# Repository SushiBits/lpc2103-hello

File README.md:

# lpc2103-hello

Firmware for the LPC2103 evaluation board in [hardware/](hardware/) — a
blinkenlight, eventually. The board is not the interesting part. The interesting
part is that a 2004-era ARM7TDMI-S is being driven through a project structure
that a freshly started Cortex-M3 project would recognise, built from open
components with exactly one exception.

## A Cortex-M project with an ARM7 inside

The LPC2103 predates CMSIS by roughly half a decade. Its core is ARM7TDMI-S,
which is ARMv4T: no NVIC, no SysTick, no CMSIS vector table, no core header,
and nothing in CMSIS-Core to include. NXP never published a CMSIS-Pack for the
LPC2000 line, and there is no vendor SVD to download — the ones that ever
existed shipped inside Keil MDK installs under a vendor licence.

None of that is hidden here, and the core layer is genuinely hand-written. But
above the core everything is laid out the way modern tooling expects:

| Modern Cortex-M habit | How this project does it |
| --- | --- |
| Device header generated from a CMSIS-SVD | [LPC2103.svd](contrib/platform/share/LPC2103.svd) → SVDConv → `LPC2103.h` |
| Interrupt handler table generated from the IRQn enum | [irqn](contrib/irqn) → `LPC2103_handlers.h` |
| `core_*.h` / `system_*.h` / device header layering | [core_arm7tdmi-s.h](contrib/platform/include/core_arm7tdmi-s.h), [system_LPC2103.h](contrib/platform/include/system_LPC2103.h) |
| Register structs, `*_Pos` / `*_Msk` macros, field enums | generated, straight from the SVD |
| Peripheral view in the debugger during bring-up | cortex-debug loading the same SVD over J-Link |
| Boot image that the chip actually starts | [lpcsum.py](contrib/platform/share/lpcsum.py) writes the vector checksum the boot loader demands |

So the device description, the register map, the interrupt table and the
debugger's peripheral view all come from one machine-readable file, the same way
they would on a Cortex-M part. The only place the 2005 is visible is the core
header: a few hundred lines of qualifiers and intrinsics restricted to what
ARMv4T can actually execute.

## The device description

[LPC2103.svd](contrib/platform/share/LPC2103.svd) is typed in by hand, section
by section, reading UM10161 — no vendor file, no conversion, no scraping. It
took around twenty late-night commits to cover the part, one peripheral per
commit: SYS, VIC, PCB, GPIO0, FIO0, UART0/1, I2C0/1, SPI, SSP, ADC, TIMER0-3,
WDT and RTC. All eighteen are described; every VIC channel the silicon
implements now has a name in the generated `IRQn_Type`.

Because the document is hand-built, the manual was treated as a source to be
checked rather than trusted. Several of its own tables disagree with each other,
and a blank LPC2103 on a J-Link settles those arguments in about a minute:

| Question | Manual | Silicon |
| --- | --- | --- |
| PCONP reset value | `0x03BE` in the register summary, `0x001817BE` in the bit table | **`0x00C8179E`** |
| `SSPRIS` reset value | `0x04` in the register map, `TXRIS` = 1 in the bit table | **`0x08`** |
| Timer 2/3 counter width | 16-bit chapter, but a 32-bit counter paragraph copied in | **16 bits** |

The SVD records the measured values, and the commit messages say where the
number came from. The one thing silicon cannot settle is register *naming* —
which is why the VIC's two `VectAddr` registers had to be disambiguated by hand.

## How the pieces are produced

```
 LPC2103.svd ──SVDConv──▶ LPC2103.h ──irqn──▶ LPC2103_handlers.h
      │                      │                      │
      │                      └── includes ──▶ core_other.h ──▶ core_arm7tdmi-s.h
      │                                      system_LPC2103.h
      │
      └── debugger peripheral view (cortex-debug)

 firmware.elf ──lpcsum.py──▶ checksum patched in, then objcopy ▶ .ihx / .bin
```

`LPC2103.h` and `LPC2103_handlers.h` are generated and therefore ignored by
git; the SVD is the source of truth, and `make headers` rebuilds both. The
hand-written headers are tracked:

- [core_arm7tdmi-s.h](contrib/platform/include/core_arm7tdmi-s.h) — the access
  qualifiers, CPSR view and intrinsics ARMv4T actually has. `MRS`, `MSR`, `SWP`
  and `RRX` exist only in ARM state, so translation units using the CPSR helpers
  must be built without `-mthumb`.
- [core_other.h](contrib/platform/include/core_other.h) — a two-line shim,
  because SVDConv emits `#include "core_other.h"` for `<cpu><name>other</name>`.
  Aliasing the name keeps the generated text untouched, with no post-processing
  step to forget.
- [system_LPC2103.h](contrib/platform/include/system_LPC2103.h) — the system
  layer interface. It is included too early to see the generated SYS macros, so
  anything touching a system register goes through the raw address.
- [lpcsum.py](contrib/platform/share/lpcsum.py) — parses the linked ELF, finds
  the vector table by address through its `PT_LOAD` segment, and writes the
  two's complement checksum the LPC2000 boot loader requires at `0x14`
  (UM10161 5.2). Without it the part stays in ISP and the firmware never runs.

## Requirements

- `arm-none-eabi-gcc` and binutils
- `make`
- `python3`
- Keil's `SVDConv.exe` for regenerating the device header
- `git submodule update --init` for [irqn](contrib/irqn)
- J-Link plus VS Code with cortex-debug, if you want the debugger view

## Status

The platform layer is complete and the SVD covers the whole device; the
firmware itself is not written yet. The [Makefile](Makefile) is carried over
from a Cortex-M0+ project and still needs retargeting to `arm7tdmi` before `make`
produces anything — `-mcpu=cortex-m0plus -mthumb` is not this core.

## Licence

The project is BSD 3-Clause; see [LICENSE.md](LICENSE.md).

Third-party material keeps its own terms:

- **NXP documentation** in [docs/](docs/) is NXP's, redistributed for reference
  and not covered by the project licence. The SVD in this repository is not
  derived from it mechanically; it is a transcription of the register
  descriptions, which is exactly the kind of use the documentation invites.
- **Arm CMSIS** — the structure, naming and intent of
  [core_arm7tdmi-s.h](contrib/platform/include/core_arm7tdmi-s.h) follow CMSIS
  Core, which is Apache-2.0. The bodies are reimplemented for ARMv4T; none of
  the CMSIS headers are vendored.
- **Keil SVDConv** is proprietary and not redistributed here. It is the only
  closed-source component in the toolchain, and it runs from an existing Keil
  installation. Everything else — the compiler, the linker, `make`, Python,
  KiCad, VS Code, cortex-debug — is open source.

## Trademarks

See [TRADEMARKS.md](TRADEMARKS.md).

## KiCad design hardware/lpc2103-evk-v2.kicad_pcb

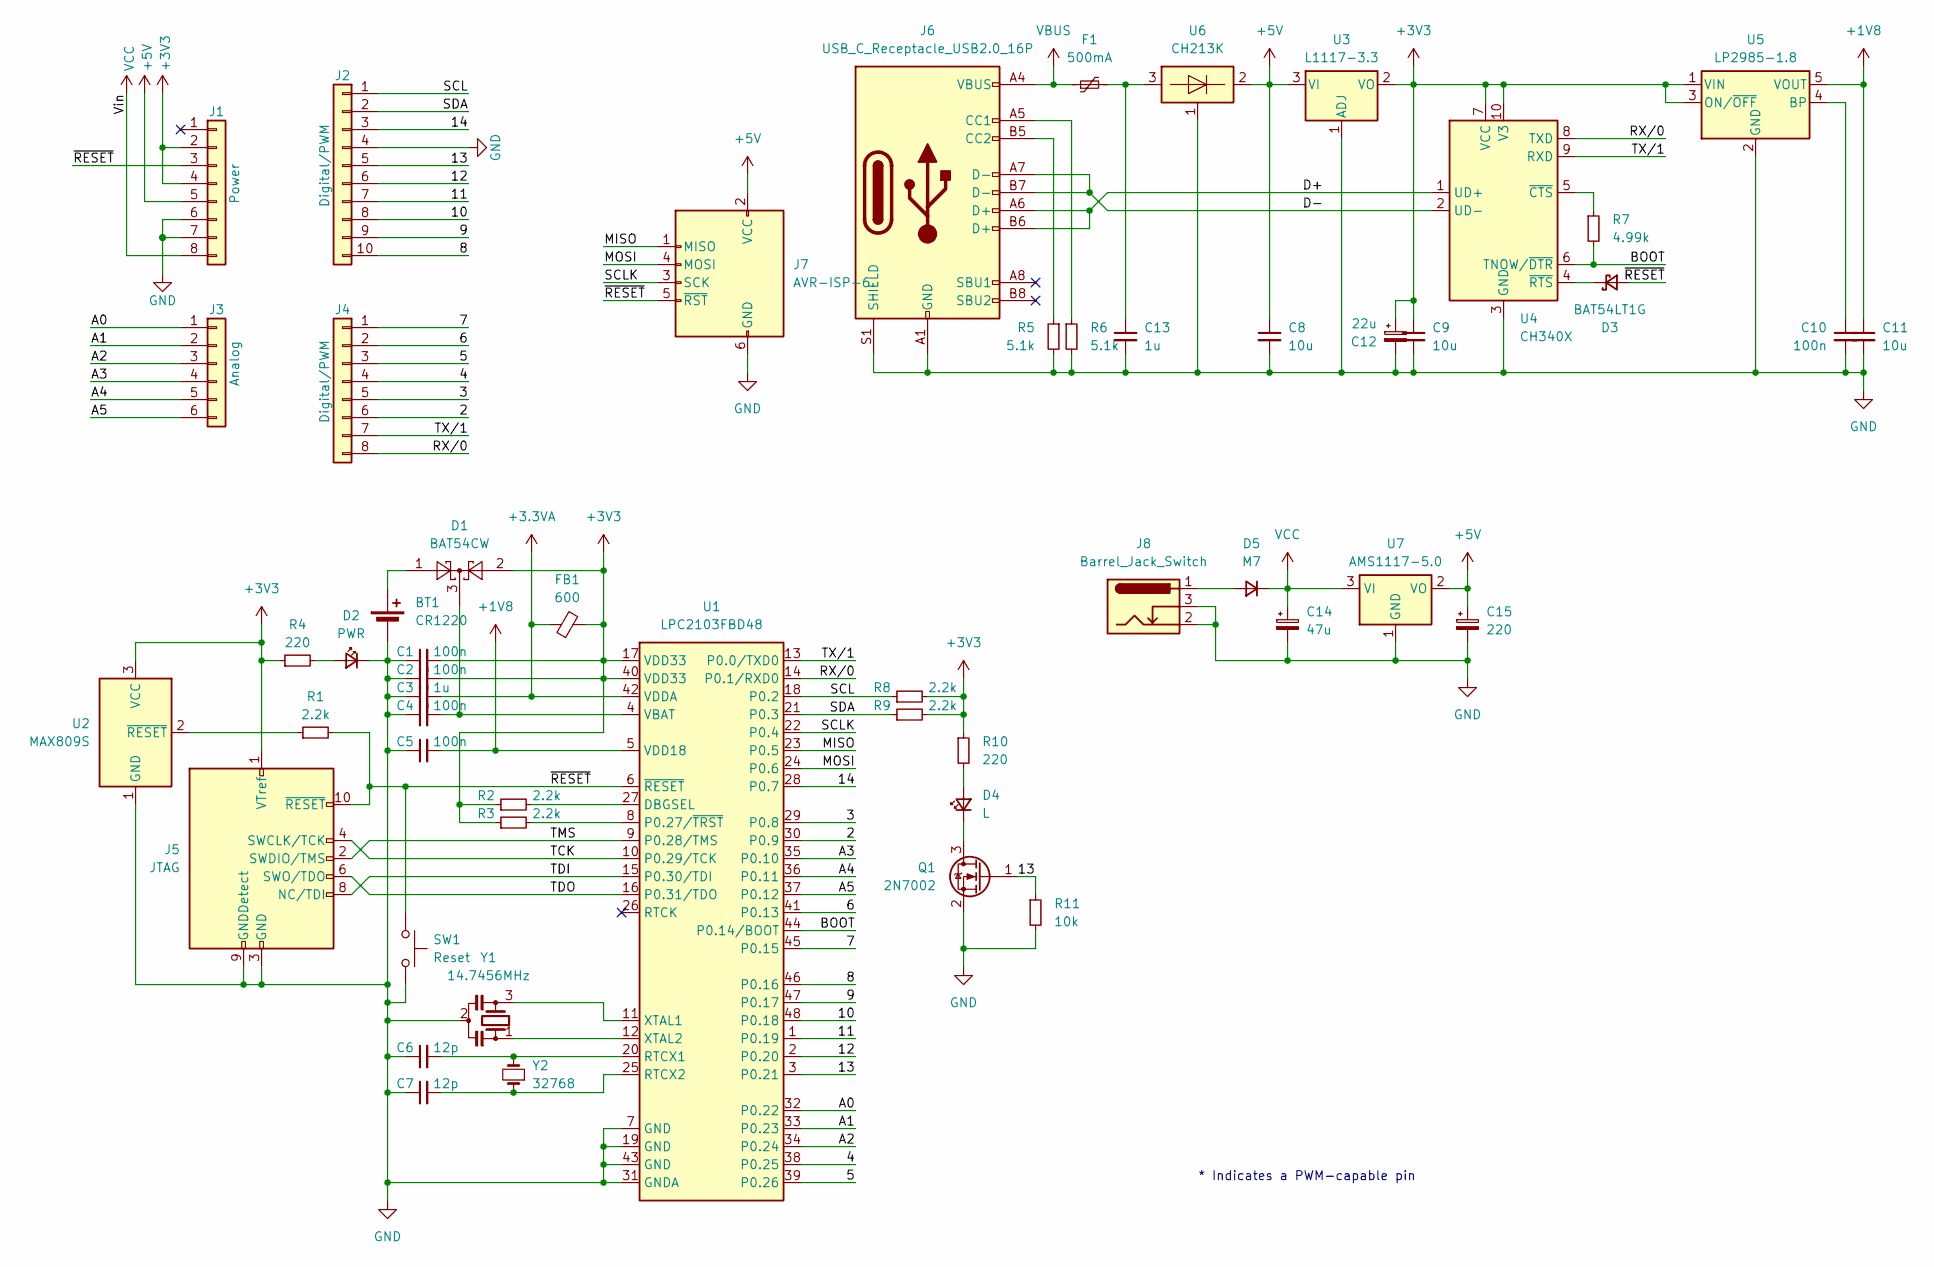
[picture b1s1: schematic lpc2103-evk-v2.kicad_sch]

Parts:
BT1: CR1220; BatteryHolder_MYoung_BS-12-B_1x1220
C1, C2, C4, C5, C10: 100n; C_0603_1608Metric_Pad1.08x0.95mm_HandSolder
C3, C13: 1u; C_0603_1608Metric_Pad1.08x0.95mm_HandSolder
C6, C7: 12p; C_0603_1608Metric_Pad1.08x0.95mm_HandSolder
C8, C9, C11: 10u; C_0603_1608Metric_Pad1.08x0.95mm_HandSolder
C12: 22u; CP_EIA-3216-10_Kemet-I
C14: 47u; CP_Elec_6.3x4.5
C15: 220; CP_EIA-3216-10_Kemet-I
D1: BAT54CW; SOT-23
D2: PWR; LED_0805_2012Metric_Pad1.15x1.40mm_HandSolder
D3: BAT54LT1G; D_SOD-323
D4: L; LED_0805_2012Metric_Pad1.15x1.40mm_HandSolder
D5: M7; D_SMA
F1: 500mA; Fuse_0805_2012Metric_Pad1.15x1.40mm_HandSolder
FB1: 600; Fuse_0603_1608Metric_Pad1.05x0.95mm_HandSolder
J1: Power; PinSocket_1x08_P2.54mm_Vertical
J2: Digital/PWM; PinSocket_1x10_P2.54mm_Vertical
J3: Analog; PinSocket_1x06_P2.54mm_Vertical
J4: Digital/PWM; PinSocket_1x08_P2.54mm_Vertical
J5: JTAG; PinHeader_2x05_P1.27mm_Vertical
J6: USB_C_Receptacle_USB2.0_16P; USB_C_Receptacle_HRO_TYPE-C-31-M-12
J7: AVR-ISP-6; PinHeader_2x03_P2.54mm_Vertical
J8: Barrel_Jack_Switch; BarrelJack_Wuerth_6941xx301002
Q1: 2N7002; SOT-23
R1, R2, R3, R8, R9: 2.2k; R_0603_1608Metric_Pad0.98x0.95mm_HandSolder
R4, R10: 220; R_0603_1608Metric_Pad0.98x0.95mm_HandSolder
R5, R6: 5.1k; R_0603_1608Metric_Pad0.98x0.95mm_HandSolder
R7: 4.99k; R_0603_1608Metric_Pad0.98x0.95mm_HandSolder
R11: 10k; R_0603_1608Metric_Pad0.98x0.95mm_HandSolder
SW1: Reset; SW_PUSH_6mm
U1: LPC2103FBD48; LQFP-48_7x7mm_P0.5mm
U2: MAX809S; SOT-23
U3: L1117-3.3; SOT-89-3
U4: CH340X; MSOP-10_3x3mm_P0.5mm
U5: LP2985-1.8; SOT-23-5
U6: CH213K; SOT-23-3
U7: AMS1117-5.0; SOT-223-3_TabPin2
Y1: 14.7456MHz; Resonator_SMD_Murata_CSTxExxV-3Pin_3.0x1.1mm
Y2: 32768; Crystal_SMD_3215-2Pin_3.2x1.5mm

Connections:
+1V8: C5.2, C11.1, U1.5 (VDD18), U5.5 (VOUT)
+3.3VA: C3.2, FB1.1, U1.42 (VDDA)
+3V3: C1.2, C2.2, C9.1, C12.1, D1.2, FB1.2, J1.2, J1.4, J5.1 (VTref), R2.1, R3.1, R4.1, R8.2, R9.2, R10.1, U1.17 (VDD33), U1.40 (VDD33), U2.3 (VCC), U3.2 (VO), U4.7 (VCC), U4.10 (V3), U5.1 (VIN), U5.3 (ON/~OFF)
+5V: C8.1, C15.1, J1.5, J7.2 (VCC), U3.3 (VI), U6.2, U7.2 (VO)
/2: J4.6, U1.30 (P0.9)
/3: J4.5, U1.29 (P0.8)
/4: J4.4, U1.38 (P0.25)
/5: J4.3, U1.39 (P0.26)
/6: J4.2, U1.41 (P0.13)
/7: J4.1, U1.45 (P0.15)
/8: J2.10, U1.46 (P0.16)
/9: J2.9, U1.47 (P0.17)
/10: J2.8, U1.48 (P0.18)
/11: J2.7, U1.1 (P0.19)
/12: J2.6, U1.2 (P0.20)
/13: J2.5, Q1.1 (G), R11.1, U1.3 (P0.21)
/14: J2.3, U1.28 (P0.7)
/A0: J3.1, U1.32 (P0.22)
/A1: J3.2, U1.33 (P0.23)
/A2: J3.3, U1.34 (P0.24)
/A3: J3.4, U1.35 (P0.10)
/A4: J3.5, U1.36 (P0.11)
/A5: J3.6, U1.37 (P0.12)
/BOOT: R7.2, U1.44 (P0.14/BOOT), U4.6 (TNOW/~DTR)
/D+: J6.A6 (D+), J6.B6 (D+), U4.1 (UD+)
/D-: J6.A7 (D-), J6.B7 (D-), U4.2 (UD-)
/MISO: J7.1 (MISO), U1.23 (P0.5)
/MOSI: J7.4 (MOSI), U1.24 (P0.6)
/RX/0: J4.8, U1.14 (P0.1/RXD0), U4.8 (TXD)
/SCL: J2.1, R8.1, U1.18 (P0.2)
/SCLK: J7.3 (SCK), U1.22 (P0.4)
/SDA: J2.2, R9.1, U1.21 (P0.3)
/TCK: J5.4 (SWCLK/TCK), U1.10 (P0.29/TCK)
/TDI: J5.8 (NC/TDI), U1.15 (P0.30/TDI)
/TDO: J5.6 (SWO/TDO), U1.16 (P0.31/TDO)
/TMS: J5.2 (SWDIO/TMS), U1.9 (P0.28/TMS)
/TX/1: J4.7, U1.13 (P0.0/TXD0), U4.9 (RXD)
/~RESET: D3.2 (A), J1.3, J5.10 (~RESET), J7.5 (~RST), R1.2, SW1.1, U1.6 (~RESET)
GND: BT1.2 (-), C1.1, C2.1, C3.1, C4.1, C5.1, C6.1, C7.1, C8.2, C9.2, C10.2, C11.2, C12.2, C13.2, C14.2, C15.2, D2.1 (K), J1.6, J1.7, J2.4, J5.3 (GND), J5.5 (GND), J5.9 (GNDDetect), J6.A1 (GND), J6.A12 (GND), J6.B1 (GND), J6.B12 (GND), J6.S1 (SHIELD), J7.6 (GND), J8.2, J8.3, Q1.2 (S), R5.2, R6.2, R11.2, SW1.2, U1.7 (GND), U1.19 (GND), U1.31 (GNDA), U1.43 (GND), U2.1 (GND), U3.1 (ADJ), U4.3 (GND), U5.2 (GND), U6.1, U7.1 (GND), Y1.2
unnamed: BT1.1 (+), D1.1
unnamed: C13.1, F1.2, U6.3
unnamed: D2.2 (A), R4.2
unnamed: D3.1 (K), U4.4 (~RTS)
unnamed: D4.2 (A), R10.2
unnamed: D4.1 (K), Q1.3 (D)
unnamed: D5.2 (A), J8.1
unnamed: J6.A5 (CC1), R6.1
unnamed: J6.B5 (CC2), R5.1
unnamed: R2.2, U1.27 (DBGSEL)
unnamed: R3.2, U1.8 (P0.27/~TRST)
unnamed: C6.2, U1.20 (RTCX1), Y2.2
unnamed: C7.2, U1.25 (RTCX2), Y2.1
unnamed: C4.2, D1.3, U1.4 (VBAT)
unnamed: U1.11 (XTAL1), Y1.3
unnamed: U1.12 (XTAL2), Y1.1
unnamed: R1.1, U2.2 (~RESET)
unnamed: R7.1, U4.5 (~CTS)
unnamed: C10.1, U5.4 (BP)
VBUS: F1.1, J6.A4 (VBUS), J6.A9 (VBUS), J6.B4 (VBUS), J6.B9 (VBUS)
VCC: C14.1, D5.1 (K), J1.8, U7.3 (VI)

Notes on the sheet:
* Indicates a PWM-capable pin

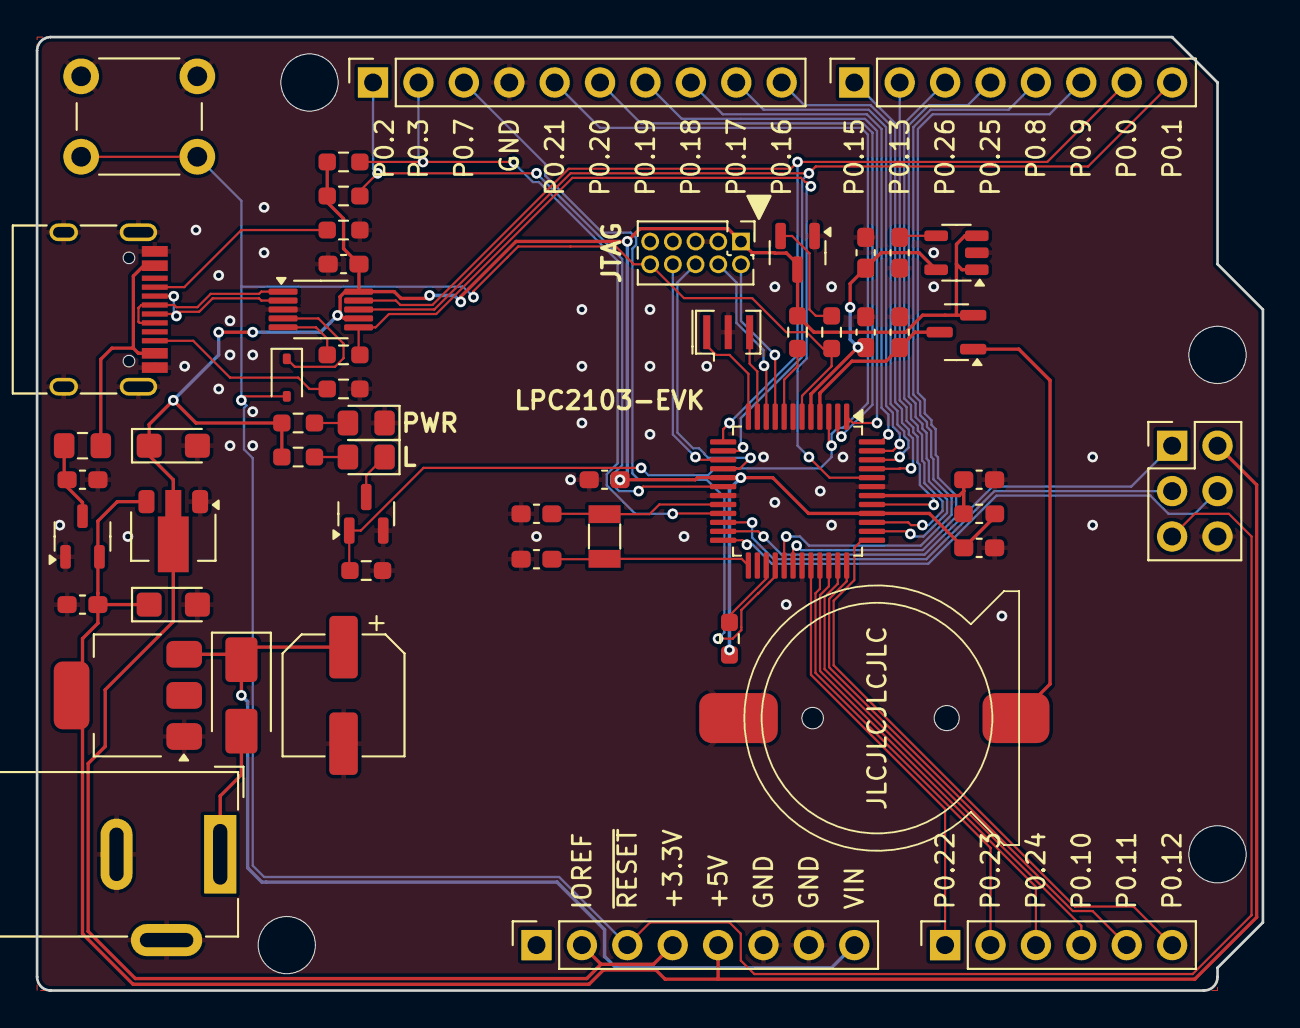
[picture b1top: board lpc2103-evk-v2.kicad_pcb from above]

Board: 2 copper layers, 68.6 x 53.3 mm, 57 parts (0 on the bottom side), 60 nets.

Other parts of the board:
MH1, MH2, MH3, MH4: MountingHole_3.2mm
